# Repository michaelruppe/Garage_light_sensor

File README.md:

# Garage Light Controller
*A quick motion-sensor project for my garage lights*

Detect motion and trigger lights - useful for arriving home at night, or not
having to turn lights off as you leave.

The control unit consists of two PIR motion sensors and one SSR switching output.

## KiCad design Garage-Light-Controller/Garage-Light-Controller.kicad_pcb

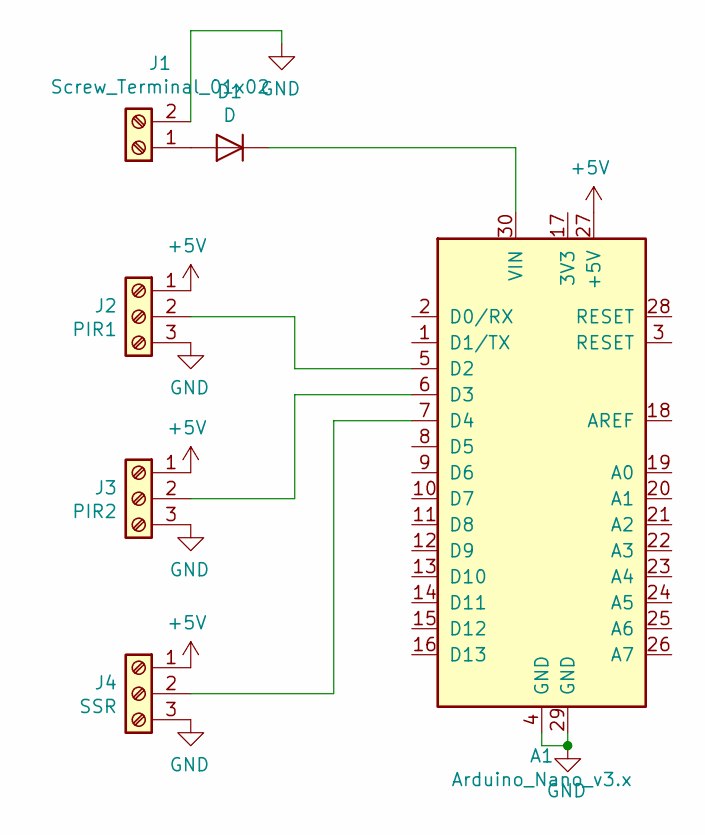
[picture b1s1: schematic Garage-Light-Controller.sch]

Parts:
A1: Arduino_Nano_v3.x; Arduino_Nano
D1: D; D_DO-34_SOD68_P7.62mm_Horizontal
J1: Screw_Terminal_01x02; SolderWirePad_1x02_P3.81mm_Drill0.8mm
J2: PIR1; SolderWirePad_1x03_P3.175mm_Drill0.8mm
J3: PIR2; SolderWirePad_1x03_P3.175mm_Drill0.8mm
J4: SSR; SolderWirePad_1x03_P3.175mm_Drill0.8mm

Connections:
+5V: A1.27 (+5V), J2.1, J3.1, J4.1
GND: A1.4 (GND), A1.29 (GND), J1.2, J2.3, J3.3, J4.3
unnamed: A1.5 (D2), J2.2
unnamed: A1.6 (D3), J3.2
unnamed: A1.7 (D4), J4.2
unnamed: A1.30 (VIN), D1.1 (K)
unnamed: D1.2 (A), J1.1

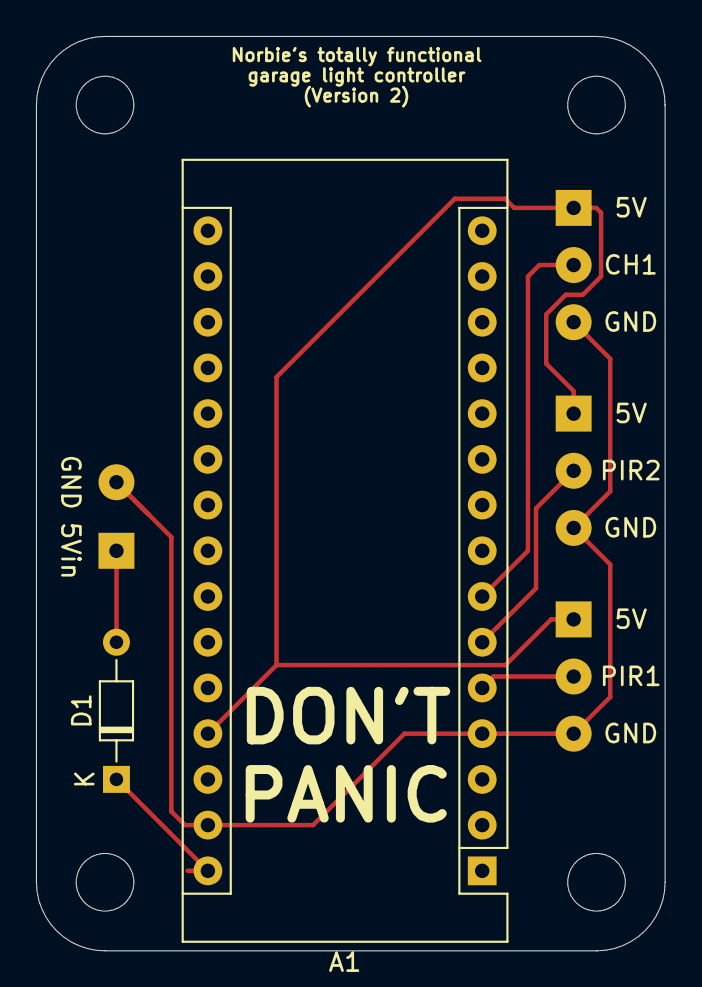
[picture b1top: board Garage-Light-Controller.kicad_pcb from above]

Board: 2 copper layers, 34.9 x 50.8 mm, 6 parts (0 on the bottom side), 7 nets.

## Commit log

2020-03-22 :hammer: initial commit
2020-04-01 :pencil2: invert output logic for another model SSR
2020-04-01 :pencil2: remove start delay
2020-04-16 :star: Version 1
    removed loop delay - it wasn't doing anything for power consumption anyway...
